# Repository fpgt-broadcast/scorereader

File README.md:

# ScoreReader

**A free replacement for Sportzcast ScoreConnect III.** Plug in your Sportzcast ScoreBot, and ScoreReader sends the live scoreboard (clock, score, period and more) to vMix, OSE, or anything else that can read a web address.

- Works with the scoreboard brands ScoreConnect supports, including Daktronics, Nevco, Fair-Play, Electro-Mech and OES.
- Runs on Windows, Mac, Linux and Raspberry Pi.
- Built after a ScoreConnect update broke the night before a game.

```
Scoreboard console ──▶ ScoreBot (USB) ──▶ ScoreReader ──▶ vMix · OSE · web dashboard
```

## Get started

**1. Get ScoreReader.** Download the version for your computer from [Releases](../../releases):

| Computer | What to do |
|---|---|
| **Windows** | Download `ScoreReader-windows-x64.zip`, right-click it and choose **Extract All**, then open the `ScoreReader` folder and double-click **ScoreReader.exe**. Keep the folder together; ScoreReader needs the files next to it. |
| **Mac** (Apple silicon) | Download `ScoreReader-macos-arm64.dmg`, open it and drag **ScoreReader** into **Applications**. The first time you open it, macOS blocks it because it isn't signed: go to **System Settings → Privacy & Security** and click **Open Anyway**. ScoreReader then runs in the menu bar (the seven-segment S icon). |
| **Linux or Raspberry Pi** | Download the source (**Code → Download ZIP**), then run `./linux/install.sh` once and `./linux/start.sh` to start. `./linux/install.sh --service` makes it start automatically at boot. |

<details><summary>Other ways to run it</summary>

- **Windows from source:** install Python 3 (tick "Add to PATH"), then use the scripts in the `windows\` folder.
- **Mac from source:** install Python 3 from python.org, then double-click `mac/Start ScoreReader.command`.
- **Linux/Pi ready-made app:** `ScoreReader-linux-x64` and `ScoreReader-linux-arm64` (Pi 4/5 on 64-bit Raspberry Pi OS) are also on Releases. Run `./linux/install.sh` from the source once anyway, for the USB permissions.
</details>

**2. Close ScoreConnect III.** It holds the ScoreBot's port. On Windows, run `windows\Stop ScoreConnect service (run as admin).bat` as administrator, or set the **ScoreConnectIII** service to *Disabled*.

**3. Plug in the ScoreBot or ScoreBridge, turn on the console, and start ScoreReader.** Open **http://localhost:8765/** (from another computer: `http://<this-computer>:8765/`).

**4. Follow the setup.** The first time, ScoreReader walks you through five steps:
1. **Connect:** it searches the network and USB and lists what it finds (a ScoreBridge, a ScoreBot, other USB-serial cables). Pick one, or choose **Other** to type an address or try the demo game.
2. **Scoreboard:** leave it on **Daktronics All Sport 5000**, which detects the sport by itself, or pick the brand, then the sport (and the console model if the brand has several).
3. **vMix:** copy the Data Source address; SetText push is optional.
4. **Network outputs:** MQTT (for OSE), JSON/CSV and the webhook.
5. **Done.** You can run it again any time from **Settings → Run setup again**.

Enter your team names on the **Teams** tab.

> **Tip:** the console only sends a value when it changes, so bump each score and the period once before the game.

No scoreboard handy? Choose **Other → Demo game** in the setup, or **Diagnostics → Demo game** (or run with `--demo`) for a pretend football game, which is handy for building graphics. Demo mode is never saved, so ScoreReader always starts with live data.

## Connect your graphics

The **Home** tab shows every address with a **Copy** button, and a green dot once something reads it.

**vMix:** in vMix, go to *Settings → Data Sources → Add → XML*, paste the address from **Home → vMix** (`http://<this-computer>:8765/data.xml`) and set the shortest refresh time. For an even faster clock, turn on **SetText push**.

**OSE and other ScoreConnect clients (MQTT):** open **Home → Network outputs**. Point them at the address shown there (port **1883**, or `ws://<this-computer>:8083/mqtt`), and set the bot number in **Settings → Network outputs → MQTT** to the one they expect. They receive the same data as from ScoreConnect.

Field names such as `clock`, `home_score`, `period` and `down_distance` are listed on the **Diagnostics** tab and in the [reference](docs/REFERENCE.md#data-fields).

## If something's wrong

| Problem | Try this |
|---|---|
| "Access is denied" or "port busy" | ScoreConnect or its service is still running. Stop it (step 2). |
| Connected, but nothing changes | Is the console on? Bump a score. Then click **Diagnostics → Re-init bot**. |
| Linux: "Permission denied" | Run `./linux/install.sh`, then unplug and replug the ScoreBot. |
| A value is wrong or missing | See [fixing a value that reads wrong](docs/REFERENCE.md#fixing-a-value-that-reads-wrong-custom_fields). |
| The setup doesn't find the ScoreBridge | Some networks block the name search (mDNS). Choose **Other → Network address** and type the bridge's IP (shown on its own page), port 10001. |
| Still stuck | Send the newest `logs/raw_*.bin` file with a description of the problem. |

The non-Daktronics brands haven't been tested on a real board yet. If yours reads wrong, the `logs/raw_*.bin` capture is what we need to fix it.

## More information

- **[Reference](docs/REFERENCE.md):** every setting, data field, MQTT detail and command-line option.
- **[How the data is decoded](docs/PROTOCOL.md):** Daktronics and the ScoreBot, plus [every other brand](docs/vendors/).
- **[Contributor notes](CLAUDE.md)** and the [changelog](CHANGELOG.md).

## Credits

- **Daktronics RTD field table:** derived from the MIT-licensed [daktronics-allsport-5000-rs](https://crates.io/crates/daktronics-allsport-5000) project (see [NOTICE](NOTICE)).
- **Other brands:** worked out from the ScoreConnect III software the owner already has, so that it can work with equipment the owner already has. No vendor code or files are included.
- **No affiliation:** ScoreReader isn't affiliated with or endorsed by Sportzcast, Genius Sports or Daktronics. Product names are trademarks of their owners.

MIT License © 2026 Jack Singewald

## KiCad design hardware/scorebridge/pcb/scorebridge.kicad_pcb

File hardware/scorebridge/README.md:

# ScoreBridge

A small box that does a ScoreBot's job without a ScoreBot. It reads the scoreboard console on a **20 mA current loop**, **RS-232** or **RS-485/422** input, and streams the raw bytes, unchanged, to ScoreReader over **Ethernet**, **Wi-Fi** or **USB**. ScoreReader decodes them exactly as it decodes data from the ScoreBot.

```
console ──DB9──► ScoreBridge ──Ethernet / Wi-Fi──► ScoreReader   Source: TCP,    host <bridge IP>, port 10001
                             └──USB-C──────────────► ScoreReader   Source: Serial, baud 115200
```

The board is a carrier for a **WT32-ETH01** module (ESP32 with Ethernet and Wi-Fi). It adds the console inputs, USB-C power and a USB serial port, four status LEDs and a DB9 connector.

> **Status: v1.0, not built yet.** The board passes KiCad's design rule check, and its schematic and layout come from the same netlist. Nothing has been fabricated, printed or flashed yet, and the firmware hasn't been compiled. Build one and test it (below) before it goes to a game. The things most likely to need a tweak are listed under [Unverified](#unverified).

## What's here

| Path | What it is |
|---|---|
| `pcb/fab/scorebridge-gerbers.zip` | **Upload this to PCBWay** (Gerbers and drill files) |
| `pcb/fab/scorebridge-bom.csv`, `pcb/fab/scorebridge-cpl.csv` | Assembly BOM and pick-and-place file (surface-mount parts only), only needed if PCBWay assembles it. `scorebridge-bom-full.csv` lists every part. |
| `pcb/scorebridge.kicad_pro` / `.kicad_pcb` / `.kicad_sch` | The KiCad 7 project. Open it to look around or to edit it. |
| `pcb/scorebridge.pdf` | Schematic, printable |
| `pcb/design.py` | The design itself: parts, nets, placement and DB9 pinout. The scripts below build everything from it. |
| `case/scorebridge_case.scad` | The case, in OpenSCAD |
| `case/stl/` | Ready-to-print `bottom.stl`, `top.stl` and `fit-coupon.stl` |
| `firmware/` | ESP32 firmware (PlatformIO, or Arduino IDE via `ScoreBridge/ScoreBridge.ino`) |
| `images/` | Renders of the board and case |

## 1. Order the board

### Bare board (PCB Instant Quote)

Upload `pcb/fab/scorebridge-gerbers.zip`.

| Setting | Value |
|---|---|
| Board type | Single pieces |
| Size | 75 × 61 mm |
| Layers | 2 |
| Material | FR-4, TG130–140 (the default) |
| Thickness | **1.6 mm** (the case is designed for this) |
| Min track / spacing | 6/6 mil (tracks are 0.25 mm, clearance 0.15 mm) |
| Min hole size | **0.3 mm** (the smallest vias) |
| Solder mask / silkscreen | Any (green / white is cheapest) |
| Surface finish | HASL lead-free. ENIG is a little better for the fine-pitch USB-C and SOIC pads if you're having it assembled. |
| Via process | Tenting vias |
| Finished copper | 1 oz |
| Edge connector, castellated holes, impedance control | No |
| Remark | "4 plated slots 0.6 mm wide for the USB-C shell legs" |

Drill sizes, if PCBWay asks:

| Holes | Sizes |
|---|---|
| Vias | 0.3 and 0.4 mm |
| Plated component holes | 0.8 (H11L1), 0.9 (LEDs), 1.0 (DB9, WT32, header), 3.2 mm (DB9 bracket) |
| Plated slots | USB-C shell, 0.6 mm wide |
| Non-plated holes | 0.65 (USB-C pegs), 3.2 mm (case screws) |

### Assembly of the small parts (optional)

PCBWay places the surface-mount parts and you solder the through-hole parts yourself: the WT32 module, H11L1, DB9 and LEDs. On the quote, add **PCB Assembly**:

| Setting | Value |
|---|---|
| Service | Turnkey (PCBWay buys the parts) |
| Sides | Top only |
| Unique parts | 20 |
| SMD parts | 39 |
| BGA/QFP | 0 |
| Through-hole parts | 0 |
| Files | Gerbers `pcb/fab/scorebridge-gerbers.zip`, BOM `pcb/fab/scorebridge-bom.csv`, centroid `pcb/fab/scorebridge-cpl.csv` |
| Remark | "Top-side SMD only, per BOM and centroid file. Do not fit U1, U3, J2, J3 or D3–D6 (customer solders). JP1/JP2 are solder jumpers, nothing to place. Equivalent parts OK for resistors, capacitors, 1N4148W and MMBT3904. SP3232EEN / SP3485EN are acceptable for U4 / U5." |

`scorebridge-bom-full.csv` lists every part, including the ones you solder. The board has no fiducials; if PCBWay asks, let them panelize it with rails and fiducials.

## 2. Parts

The full list is in `pcb/fab/scorebridge-bom.csv`. The parts worth choosing carefully:

| Part | Buy | Notes |
|---|---|---|
| U1 | **WT32-ETH01** (the original ESP32 version, *not* the "-EVO") | Get the one with header pins on the bottom. ETH02 boards use the same pinout. |
| J2 | DE-9 **male**, right angle, **with a metal bracket**, PCB mount | Its footprint needs the front pin row 7.7 mm behind the board edge and 25 mm mounting holes. Check the datasheet drawing before ordering. |
| U3 | H11L1M (DIP-6) | Optocoupler with a Schmitt trigger; this is what makes a clean current-loop input |
| U4 / U5 | MAX3232E / MAX3485E (or SP3232EEN / SP3485EN) | The 3.3 V versions |
| U2 | CH340C | USB serial; needs no crystal |
| J1 | HRO TYPE-C-31-M-12 | 16-pin USB-C |
| D3–D6 | 3 mm LEDs: red, green, yellow, orange | Bent 90° so they point out of the front edge (PWR, NET, CLIENT, DATA) |
| Case | 4× M3 × 12 mm screws, 4× M3 heat-set inserts (M3 × 5.7, 4.0 mm hole) | Or M3 self-tapping screws; set `insert_d = 2.6` in the .scad |

## 3. Assemble

1. **SMD parts first:** CH340C, MAX3232, MAX3485, USBLC6, transistors, passives, then the USB-C connector.
2. **Through-hole parts:**
   - The H11L1.
   - The four LEDs: lay them flat with the lens past the front edge, longer leg (anode) in the round pad.
   - The DB9.
   - Leave J3 empty.
3. **WT32-ETH01 last.**
   - **Check its orientation before soldering:** the RJ45 points out over the back edge, and the module's row labelled **5V / 3V3 / GND / EN** is on the USB-C side. The row with IO0, IO1 and IO3 is on the DB9 side.
   - **Seat it:** push the header pins through until the black plastic spacer sits on the board, then solder. This sets the height the case expects.
   - **Trim** the leads underneath to under 4 mm.
4. **Solder jumpers:**
   - JP1 comes bridged; leave it. It lets the USB port flash the ESP32 automatically.
   - JP2 stays open. Bridge it only if this is the last device on an RS-485 line.

## 4. Flash and set up

1. **Connect USB:** plug USB-C into a computer. The PWR LED lights and a COM port appears; Windows usually installs the CH340 driver by itself.
2. **Flash the firmware:**
   - PlatformIO: `cd firmware && pio run -t upload`.
   - Arduino IDE: install the "esp32" boards, open `firmware/ScoreBridge/ScoreBridge.ino`, choose "ESP32 Dev Module" and upload.
   - If the upload doesn't start, hold **BOOT**, tap **RESET** and release BOOT.
   - Later updates can go over the network once a **settings password** is set (then restart the box): the settings page → **Firmware update**, upload the `.bin`. Without a password the box refuses network updates, so nobody else on the network (or on its setup access point) can load their own firmware.
3. **Connect to its settings page:**
   - **On Ethernet:** plug in a cable. The NET LED goes solid once it has an address. Open `http://scorebridge.local/`, or look up its IP in your router's DHCP list.
   - **No network:** after 15 seconds it starts its own Wi-Fi network, **ScoreBridge-XXXX**, password `scorebridge`; the NET LED blinks. Join it and open `http://192.168.4.1/`.
   - **Then set a settings password and your own access point password** on that page. Until you do, anyone on the network, or anyone in the building who joins `ScoreBridge-XXXX` with the published default password, can change its settings.
4. **Pick the console:** click a preset on the settings page (Daktronics current loop, Electro-Mech current loop, Colorado Timing V1/V2, Daktronics RTD), then **Save**. The settings page shows bytes arriving, live.
5. **Set up ScoreReader:**
   - Settings → **Source: TCP**.
   - **Host:** the bridge's IP address. A fixed IP (set on the bridge's page, or a DHCP reservation) is the most reliable choice on game day.
   - **Port:** `10001`.
   - Pick the scoreboard brand as usual. The CLIENT LED lights while ScoreReader is connected.
   - Over USB instead: **Source: Serial**, its COM port, **Baud: 115200**.
   - DHCP or a static IP can also be set from ScoreReader (Settings › Scoreboard input › **ScoreBridge network**), over USB or the network, firmware 1.1+. First-run setup offers it too when the box is plugged in over USB.
6. **Check the data:** the **Last bytes** line on the bridge's page shows the raw data. Over USB, `python scorereader.py --port COM7 --baud 115200 --sniff 20` shows the same.
   - Daktronics current loop: `55 AA` frames.
   - Electro-Mech: bytes alternating between under `80` and `80`-or-over.
   - Garbage: untick or tick **Invert** on the bridge's page.

**Resetting the network settings:** power-cycle it three times within a few seconds of it starting. That clears the network settings and the settings password, and opens the setup Wi-Fi network. The BOOT button can't do this, because on the WT32 that pin carries the Ethernet clock.

## 5. Wire the console

The DB9 is male, with the pins like a PC serial port for RS-232:

| DB9 pin | Signal | Use |
|---|---|---|
| 1 | Current loop + | Daktronics / Electro-Mech scoreboard driver output |
| 6 | Current loop − | |
| 2 | RS-232 in (console TX) | Colorado Timing, Daktronics J6 RTD |
| 5 | Ground | RS-232 / RS-485 ground (**not** the current loop, which is isolated) |
| 7 | RS-485 / 422 A (+) | |
| 8 | RS-485 / 422 B (−) | |

- **Current loop:** the H11L1 isolates this input from everything else, so the console's loop and your network equipment never share a ground.
  - **Measure the port first:** a regulated 20 mA loop is what it expects (the 100 Ω resistor limits the current otherwise).
  - **If there's no data:** swap the + and − wires, or flip **Invert**.
- **Reusing the Sportzcast fan-out cable:** use a meter to find which DB9 pin goes to each plug on the fan-out. If they differ from the table, change `DB9_PINS` in `pcb/design.py` and rebuild *before* ordering boards, and the cable plugs straight in.
- **ScoreBot-decoded brands won't work:** brands where the ScoreBot's own chip decodes the data (Nevco, Daktronics All Sport 4000, Fair-Play MP-69/70) still need the ScoreBot. ScoreBridge passes raw bytes; Daktronics All Sport 5000, Electro-Mech and Colorado Timing are all raw.

## 6. Print the case

Ports, LEDs and screw ears on the case:

| Side | What's there |
|---|---|
| Back | DB9 (CONSOLE), Ethernet, USB-C |
| Front | The four LEDs |
| Left and right | Screw-down ears for a permanent install, for #8 / 4 mm countersunk screws |

The two halves are held together by four M3 screws from underneath, which also clamp the board.

1. **Print `case/stl/fit-coupon.stl` first** (just the back wall, about 15 minutes) and hold it against the assembled board. If a cut-out is off, adjust the heights at the top of `scorebridge_case.scad` (`DB9_Z`, `USB_Z`, `RJ45_BOTTOM` …) and re-export.
2. **Print `bottom.stl` and `top.stl`:** PETG or PLA, 0.2 mm layers, 3 walls, no supports. Both are already oriented for printing.
3. **Fit the inserts:** press the heat-set inserts into the four posts in the lid.
4. **Prepare the DB9:** unscrew the DB9's two hex screwlocks.
5. **Close it up:** drop the board into the bottom half, put the lid on and fit the four M3 screws from underneath.
6. **Refit the screwlocks** from the outside, through the back wall; this also holds the connector to the case.

Exporting the STLs again after a change:

```bash
cd case
for p in bottom top coupon; do openscad -D "part=\"$p\"" -o stl/$p.stl scorebridge_case.scad; done
```

## Firmware reference

| | |
|---|---|
| TCP port | 10001 (changeable). Raw bytes to every connected client, up to 4 at once, so two ScoreReader machines can share one console. |
| USB | Raw bytes at 115200 (can be turned off on the settings page) |
| LEDs | **PWR** power · **NET** solid = Ethernet or Wi-Fi up, blinking = setup Wi-Fi network · **CLIENT** ScoreReader connected · **DATA** flickers with every byte from the console |
| `GET /api/status` | JSON: network, clients, input settings, byte counters, the last bytes in hex |
| `POST /api/serial` | `input=cl\|rs232\|rs485&baud=19200&invert=1&format=8N1[&save=1]`: switch the input without the page (meant for ScoreReader to set it from the chosen scoreboard later) |
| Settings password | Optional (user `admin`); also protects firmware updates |

## Rebuilding the design files

Everything is generated from `pcb/design.py`, so edit that, never the KiCad files by hand, unless you're finishing the routing in KiCad yourself.

```bash
cd pcb
./build.sh                 # KiCad 7: place, autoroute (route.py), ground pours, DRC, Gerbers/BOM/CPL in fab/
python3 make_sch.py        # schematic (pip install kiutils==1.4.8)
kicad-cli sch export netlist -o /tmp/sb.net scorebridge.kicad_sch && python3 check_netlist.py /tmp/sb.net
```

`route.py` is a small autorouter written for this board. Its routing is valid (DRC-clean) but not pretty. You can rip up and reroute anything in KiCad and then run `./build.sh --no-route` to regenerate the fab files from your edits.

## Unverified

- **WT32-ETH01 position and size:** the pin positions come from the datasheet's pin table and the community footprint at github.com/egnor/wt32-eth01. Sources disagree on how far the RJ45 overhangs the module's edge (5–8 mm), so the case cut-out allows for either. Check with the fit coupon.
- **DB9 shell height:** assumed 6.3 mm above the board (`DB9_Z`); it depends on the connector you buy. Check with the fit coupon.
- **Firmware:** not compiled yet, because the ESP32 toolchain couldn't be downloaded in the environment where it was written. It targets the Arduino-ESP32 core 2.0.x and 3.x; the first `pio run` will show any typo.
- **Current-loop polarity and Invert:** what the Daktronics and Electro-Mech loops need with this optocoupler is a guess (the ScoreBot reads both inverted). Flipping the setting is free.
- **Routing:** the board is autorouted. It passes DRC, but a person should look it over, especially the USB pair, before ordering a big batch.

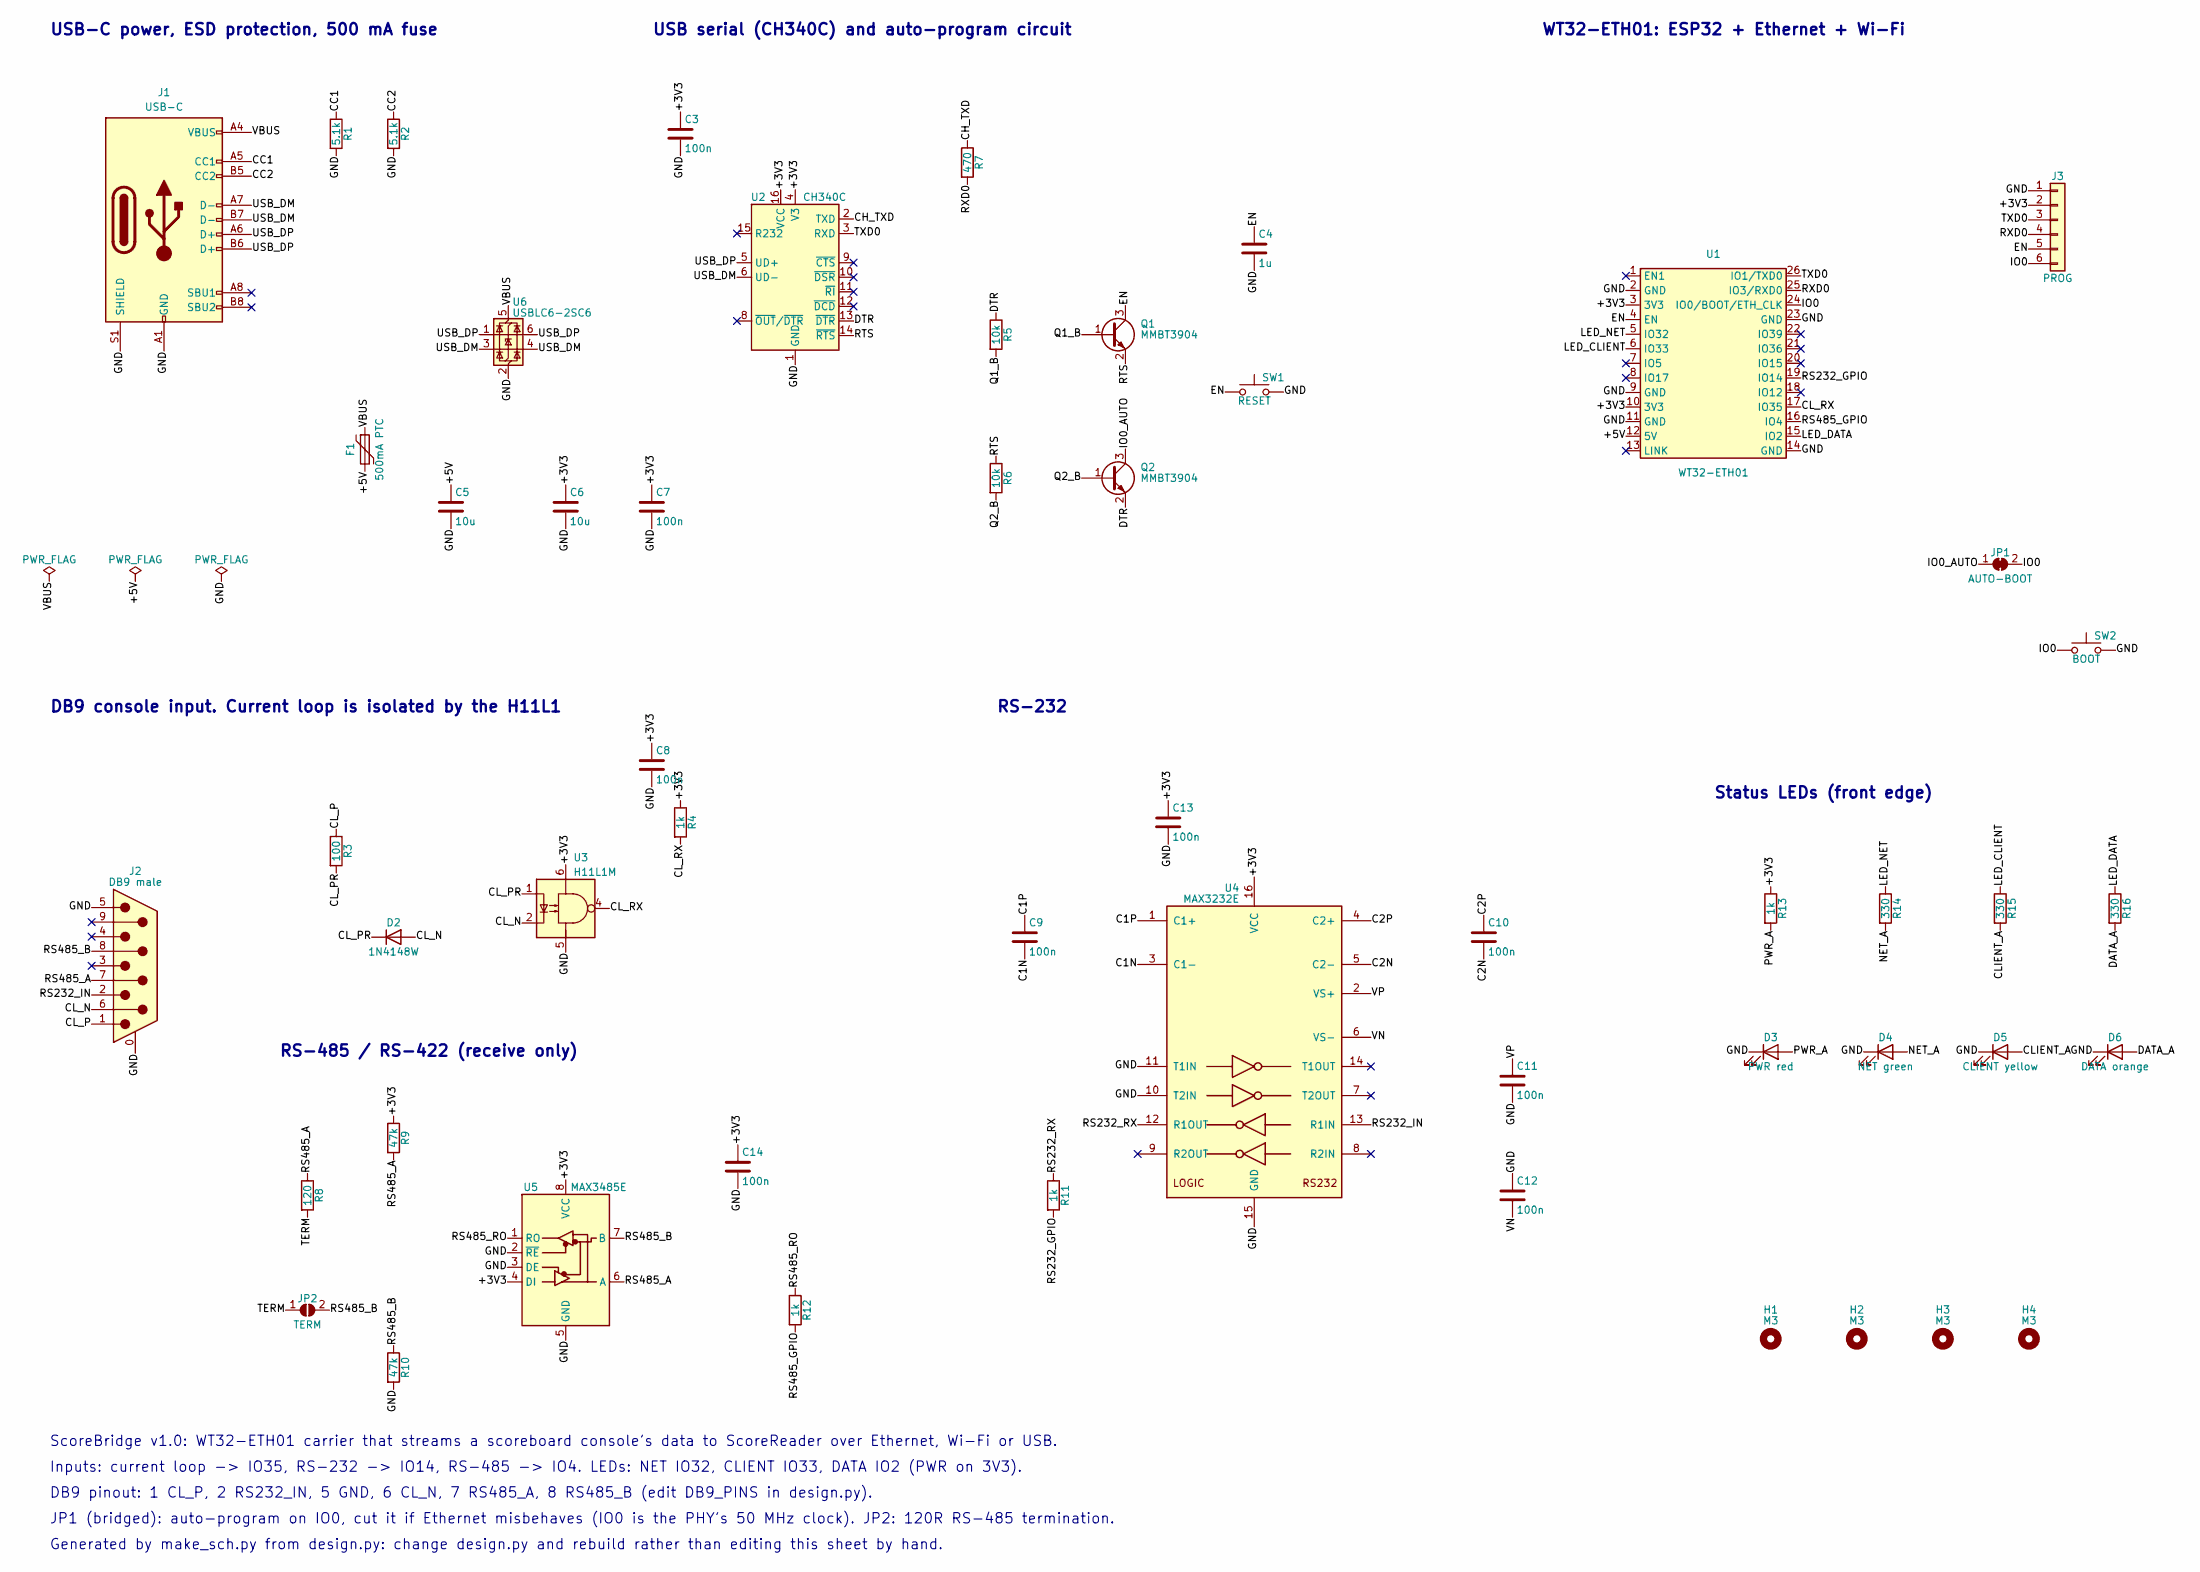
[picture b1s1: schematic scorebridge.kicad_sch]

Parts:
C3, C7, C8, C9, C10, C11, C12, C13, C14: 100n; C_0805_2012Metric
C4: 1u; C_0805_2012Metric
C5, C6: 10u; C_0805_2012Metric
D2: 1N4148W; D_SOD-123; MPN 1N4148W
D3: PWR red; LED_D3.0mm_Horizontal_O1.27mm_Z2.0mm; MPN 3 mm red LED
D4: NET green; LED_D3.0mm_Horizontal_O1.27mm_Z2.0mm; MPN 3 mm green LED
D5: CLIENT yellow; LED_D3.0mm_Horizontal_O1.27mm_Z2.0mm; MPN 3 mm yellow LED
D6: DATA orange; LED_D3.0mm_Horizontal_O1.27mm_Z2.0mm; MPN 3 mm orange LED
F1: 500mA PTC; Fuse_1206_3216Metric; MPN MF-NSMF050-2
H1, H2, H3, H4: M3; MountingHole_3.2mm_M3
J1: USB-C; USB_C_Receptacle_HRO_TYPE-C-31-M-12; MPN TYPE-C-31-M-12
J2: DB9 male; DSUB-9_Male_Horizontal_P2.77x2.84mm_EdgePinOffset7.70mm_Hou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
J3: PROG; PinHeader_1x06_P2.54mm_Vertical
JP1: AUTO-BOOT; SolderJumper-2_P1.3mm_Bridged_RoundedPad1.0x1.5mm
JP2: TERM; SolderJumper-2_P1.3mm_Open_RoundedPad1.0x1.5mm
Q1, Q2: MMBT3904; SOT-23; MPN MMBT3904
R1, R2: 5.1k; R_0805_2012Metric
R3: 100; R_1206_3216Metric
R4, R11, R12, R13: 1k; R_0805_2012Metric
R5, R6: 10k; R_0805_2012Metric
R7: 470; R_0805_2012Metric
R8: 120; R_0805_2012Metric
R9, R10: 47k; R_0805_2012Metric
R14, R15, R16: 330; R_0805_2012Metric
SW1: RESET; SW_Push_1P1T_NO_CK_KMR2; MPN KMR221GLFS
SW2: BOOT; SW_Push_1P1T_NO_CK_KMR2; MPN KMR221GLFS
U1: WT32-ETH01; MPN WT32-ETH01
U2: CH340C; SOIC-16_3.9x9.9mm_P1.27mm; MPN CH340C
U3: H11L1M; DIP-6_W7.62mm; MPN H11L1M
U4: MAX3232E; SOIC-16_3.9x9.9mm_P1.27mm; MPN MAX3232EESE+
U5: MAX3485E; SOIC-8_3.9x4.9mm_P1.27mm; MPN MAX3485EESA+
U6: USBLC6-2SC6; SOT-23-6; MPN USBLC6-2SC6

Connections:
+3V3: C3.1, C6.1, C7.1, C8.1, C13.1, C14.1, J3.2, R4.1, R9.1, R13.1, U1.3 (3V3), U1.10 (3V3), U2.4 (V3), U2.16 (VCC), U3.6, U4.16 (VCC), U5.4 (DI), U5.8 (VCC)
+5V: C5.1, F1.2, U1.12 (5V)
C1N: C9.2, U4.3 (C1-)
C1P: C9.1, U4.1 (C1+)
C2N: C10.2, U4.5 (C2-)
C2P: C10.1, U4.4 (C2+)
CC1: J1.A5 (CC1), R1.1
CC2: J1.B5 (CC2), R2.1
CH_TXD: R7.1, U2.2 (TXD)
CLIENT_A: D5.2 (A), R15.2
CL_N: D2.2 (A), J2.6, U3.2
CL_P: J2.1, R3.1
CL_PR: D2.1 (K), R3.2, U3.1
CL_RX: R4.2, U1.17 (IO35), U3.4
DATA_A: D6.2 (A), R16.2
DTR: Q2.2 (E), R5.1, U2.13 (~DTR)
EN: C4.1, J3.5, Q1.3 (C), SW1.1, U1.4 (EN)
GND: C3.2, C4.2, C5.2, C6.2, C7.2, C8.2, C11.2, C12.1, C13.2, C14.2, D3.1 (K), D4.1 (K), D5.1 (K), D6.1 (K), J1.A1 (GND), J1.A12 (GND), J1.B1 (GND), J1.B12 (GND), J1.S1 (SHIELD), J2.0 (PAD), J2.5, J3.1, R1.2, R2.2, R10.2, SW1.2, SW2.2, U1.2 (GND), U1.9 (GND), U1.11 (GND), U1.14 (GND), U1.23 (GND), U2.1 (GND), U3.5, U4.10 (T2IN), U4.11 (T1IN), U4.15 (GND), U5.2 (~RE), U5.3 (DE), U5.5 (GND), U6.2 (GND)
IO0: J3.6, JP1.2 (B), SW2.1, U1.24 (IO0/BOOT/ETH_CLK)
IO0_AUTO: JP1.1 (A), Q2.3 (C)
LED_CLIENT: R15.1, U1.6 (IO33)
LED_DATA: R16.1, U1.15 (IO2)
LED_NET: R14.1, U1.5 (IO32)
NET_A: D4.2 (A), R14.2
PWR_A: D3.2 (A), R13.2
Q1_B: Q1.1 (B), R5.2
Q2_B: Q2.1 (B), R6.2
RS232_GPIO: R11.2, U1.19 (IO14)
RS232_IN: J2.2, U4.13 (R1IN)
RS232_RX: R11.1, U4.12 (R1OUT)
RS485_A: J2.7, R8.1, R9.2, U5.6 (A)
RS485_B: J2.8, JP2.2 (B), R10.1, U5.7 (B)
RS485_GPIO: R12.2, U1.16 (IO4)
RS485_RO: R12.1, U5.1 (RO)
RTS: Q1.2 (E), R6.1, U2.14 (~RTS)
RXD0: J3.4, R7.2, U1.25 (IO3/RXD0)
TERM: JP2.1 (A), R8.2
TXD0: J3.3, U1.26 (IO1/TXD0), U2.3 (RXD)
USB_DM: J1.A7 (D-), J1.B7 (D-), U2.6 (UD-), U6.3 (I/O2), U6.4 (I/O2)
USB_DP: J1.A6 (D+), J1.B6 (D+), U2.5 (UD+), U6.1 (I/O1), U6.6 (I/O1)
VBUS: F1.1, J1.A4 (VBUS), J1.A9 (VBUS), J1.B4 (VBUS), J1.B9 (VBUS), U6.5 (VBUS)
VN: C12.2, U4.6 (VS-)
VP: C11.1, U4.2 (VS+)

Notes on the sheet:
USB-C power, ESD protection, 500 mA fuse
USB serial (CH340C) and auto-program circuit
WT32-ETH01: ESP32 + Ethernet + Wi-Fi
DB9 console input. Current loop is isolated by the H11L1
RS-485 / RS-422 (receive only)
RS-232
Status LEDs (front edge)
ScoreBridge v1.0: WT32-ETH01 carrier that streams a scoreboard console's data to ScoreReader over Ethernet, Wi-Fi or USB.
Inputs: current loop -> IO35, RS-232 -> IO14, RS-485 -> IO4. LEDs: NET IO32, CLIENT IO33, DATA IO2 (PWR on 3V3).
DB9 pinout: 1 CL_P, 2 RS232_IN, 5 GND, 6 CL_N, 7 RS485_A, 8 RS485_B (edit DB9_PINS in design.py).
JP1 (bridged): auto-program on IO0, cut it if Ethernet misbehaves (IO0 is the PHY's 50 MHz clock). JP2: 120R RS-485 termination.
Generated by make_sch.py from design.py: change design.py and rebuild rather than editing this sheet by hand.

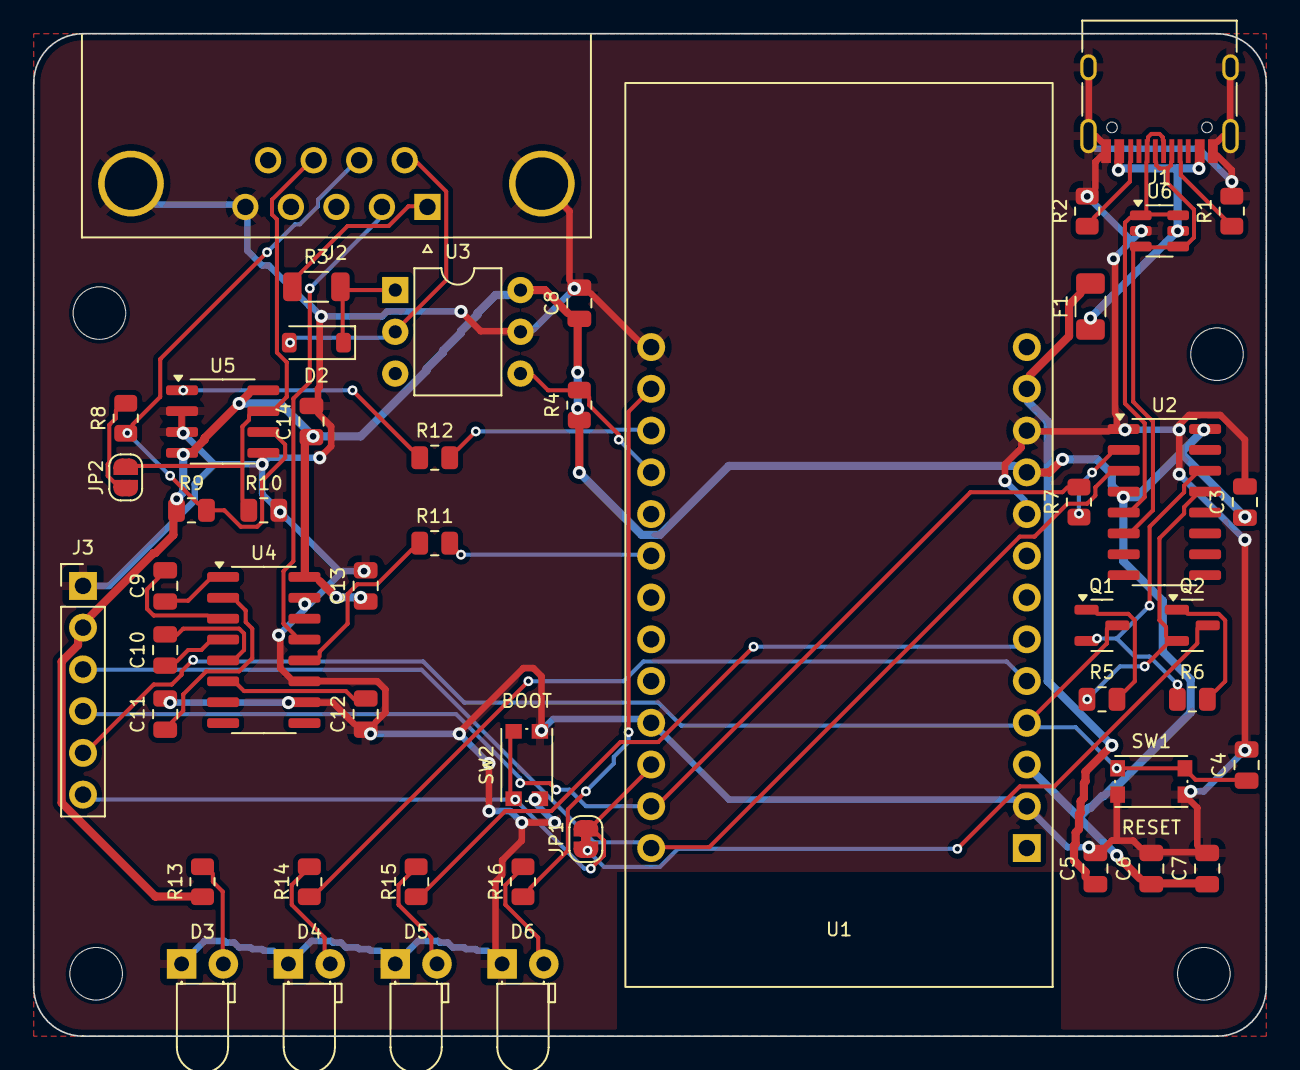
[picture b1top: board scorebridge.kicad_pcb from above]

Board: 2 copper layers, 75.0 x 61.0 mm, 53 parts (0 on the bottom side), 43 nets.

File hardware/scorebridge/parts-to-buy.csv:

Mfg Part #,Manufacturer,Description,Per board,Buy (5 boards + spares),Designators,Notes
CL21B104KBCNNNC,Samsung,"Capacitor 100nF 50V X7R 0805",9,100,"C3,C7-C14","any 0805 100nF X7R works"
CL21B105KBFNNNE,Samsung,"Capacitor 1uF 50V X7R 0805",1,20,C4,"any 0805 1uF works"
CL21A106KAYNNNE,Samsung,"Capacitor 10uF 25V X5R 0805",2,20,"C5,C6","any 0805 10uF 10V+ works"
RC0805FR-075K1L,Yageo,"Resistor 5.1k 1% 0805",2,20,"R1,R2","USB-C CC pull-downs"
RC0805FR-071KL,Yageo,"Resistor 1k 1% 0805",4,50,"R4,R11,R12,R13",
RC0805FR-0710KL,Yageo,"Resistor 10k 1% 0805",2,20,"R5,R6",
RC0805FR-07470RL,Yageo,"Resistor 470R 1% 0805",1,10,R7,
RC0805FR-07120RL,Yageo,"Resistor 120R 1% 0805",1,10,R8,"RS-485 termination (only used if JP2 bridged)"
RC0805FR-0747KL,Yageo,"Resistor 47k 1% 0805",2,20,"R9,R10",
RC0805FR-07330RL,Yageo,"Resistor 330R 1% 0805",3,20,"R14,R15,R16",
RC1206FR-07100RL,Yageo,"Resistor 100R 1% 1206",1,10,R3,"current-loop series resistor"
1N4148W-7-F,Diodes Inc,"Diode 1N4148W SOD-123",1,10,D2,
MMBT3904LT1G,onsemi,"NPN transistor MMBT3904 SOT-23",2,20,"Q1,Q2",
MF-NSMF050-2,Bourns,"PTC resettable fuse 0.5A hold 1206",1,10,F1,
TYPE-C-31-M-12,HRO (Korean Hroparts),"USB-C receptacle 16-pin SMD",1,8,J1,"buy extras: the hardest part to hand-solder"
USBLC6-2SC6,STMicroelectronics,"USB ESD protection SOT-23-6",1,7,U6,
CH340C,WCH,"USB to UART bridge SOIC-16 (no crystal)",1,6,U2,"must be the C version"
SP3232EEN-L/TR,MaxLinear,"RS-232 transceiver 3.3V SOIC-16 narrow",1,6,U4,"MAX3232 equivalent, same pinout"
SP3485EN-L/TR,MaxLinear,"RS-485 transceiver 3.3V SOIC-8",1,6,U5,"MAX3485 equivalent, same pinout"
KMR221GLFS,C&K,"Tactile switch 4.2x2.8mm SMD",2,12,"SW1,SW2","RESET and BOOT"
H11L1M,onsemi,"Optocoupler Schmitt trigger DIP-6",1,6,U3,"through-hole"
(see notes),any,"DB9 male right-angle PCB mount, metal bracket, #4-40 inserts",1,5,J2,"check drawing: pins 6-9 row 7.7 mm and pins 1-5 row 10.54 mm behind board edge; mounting holes 25 mm apart, 9.12 mm behind edge"
(generic),any,"LED 3mm diffused red",1,10,D3,"PWR"
(generic),any,"LED 3mm diffused green",1,10,D4,"NET"
(generic),any,"LED 3mm diffused yellow",1,10,D5,"CLIENT"
(generic),any,"LED 3mm diffused orange",1,10,D6,"DATA"
WT32-ETH01,Wireless-Tag,"ESP32 + Ethernet module",1,5,U1,"Amazon/AliExpress; original, not -EVO; header pins on the bottom"
(generic),any,"M3 x 12 mm screw (socket or button head)",4,20,case,
(generic),any,"M3 heat-set insert, M3 x 5.7 mm, for 4.0 mm hole",4,20,case,"or skip and use M3 self-tapping screws (set insert_d = 2.6 in the .scad)"

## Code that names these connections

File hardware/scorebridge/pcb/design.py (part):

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DB9_PINS = {
    1: "CL_P",      # current loop +  (into the H11L1 LED)
    6: "CL_N",      # current loop -
    2: "RS232_IN",  # RS-232 data from the console (PC RXD pin)
    5: "GND",
    7: "RS485_A",   # RS-485 / RS-422 A (non-inverting)
    8: "RS485_B",   # RS-485 / RS-422 B (inverting)
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    2: "GND", 3: "+3V3", 4: "EN", 9: "GND", 10: "+3V3", 11: "GND", 12: "+5V",
    5: "LED_NET",        # IO32
    6: "LED_CLIENT",     # IO33
    14: "GND", 15: "LED_DATA",   # IO2 (strapping pin: the LED to GND keeps it low, which is what flashing needs)
    16: "RS485_GPIO",    # IO4
    17: "CL_RX",         # IO35 (input only)
    19: "RS232_GPIO",    # IO14
    23: "GND", 24: "IO0", 25: "RXD0", 26: "TXD0",
}, "WT32-ETH01", "Wireless-Tag; buy the version with header pins on the bottom")

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     {1: "TERM", 2: "RS485_B"}, note="bridge only at the end of an RS-485 line")
part("R9", "47k", R0805, "Device:R", (9.6, 29.0, 0), {1: "+3V3", 2: "RS485_A"}, note="idle bias")
part("R10", "47k", R0805, "Device:R", (14.0, 29.0, 0), {1: "RS485_B", 2: "GND"}, note="idle bias")
part("R12", "1k", R0805, "Device:R", (24.4, 25.8, 0), {1: "RS485_RO", 2: "RS485_GPIO"})

# --- RS-232 input
part("U4", "MAX3232E", "Package_SO:SOIC-16_3.9x9.9mm_P1.27mm", "Interface_UART:MAX3232", (14.0, 37.5, 0), {
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part("C11", "100n", C0805, "Device:C", (8.0, 41.4, 90), {1: "VP", 2: "GND"})
part("C12", "100n", C0805, "Device:C", (20.2, 41.4, 90), {1: "GND", 2: "VN"})
part("C13", "100n", C0805, "Device:C", (20.2, 33.6, 90), {1: "+3V3", 2: "GND"})
part("R11", "1k", R0805, "Device:R", (24.4, 31.0, 0), {1: "RS232_RX", 2: "RS232_GPIO"})

# --- DB9 data connector
part("J2", "DB9 male", "Connector_Dsub:DSUB-9_Male_Horizontal_P2.77x2.84mm_EdgePinOffset7.70mm_Housed_MountingHolesOffset9.12mm",
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
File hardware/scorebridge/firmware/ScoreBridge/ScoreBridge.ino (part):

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static const int PIN_IN_CL = 35;
static const int PIN_IN_232 = 14;
static const int PIN_IN_485 = 4;
static const int PIN_LED_NET = 32;
static const int PIN_LED_CLIENT = 33;
static const int PIN_LED_DATA = 2;
// WT32-ETH01 Ethernet: LAN8720, PHY address 1, MDC 23, MDIO 18, oscillator enabled by GPIO16, clock into GPIO0
static const int ETH_ADDR = 1, ETH_POWER = 16, ETH_MDC = 23, ETH_MDIO = 18;

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void updateLeds() {
  uint32_t now = millis();
  bool netUp = ethUp || staUp;
  digitalWrite(PIN_LED_NET, netUp ? HIGH : (apOn ? ((now / 500) & 1) : LOW));  // blinks in setup-AP mode
  digitalWrite(PIN_LED_CLIENT, clientCount() > 0 ? HIGH : LOW);
  digitalWrite(PIN_LED_DATA, (lastByteMs && now - lastByteMs < 30) ? HIGH : LOW);
}

// ---------------------------------------------------------------- main
void setup() {
  bootMs = millis();
  pinMode(PIN_LED_NET, OUTPUT);
  pinMode(PIN_LED_CLIENT, OUTPUT);
  pinMode(PIN_LED_DATA, OUTPUT);
  loadSettings();
  Serial.begin(115200);
  checkResetGesture();
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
